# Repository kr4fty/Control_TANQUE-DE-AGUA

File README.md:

# Control de carga para TANQUE DE AGUA
 La función del circuito es la de encender/apagar un motor el cual llena un<br>
 tanque de agua. Sería reemplazo directo a los conocidos flotadores mecánicos.
<br>

<br>
## Objetivo
 El objetivo es la realización de un circuito que controle al motor, logrando<br>
 el llenado del tanque con la menor cantidad de encendidas. De esta forma se<br>
 intenta ahorrar energía, ya que al encender el motor este consume unas 6 veces<br>
 la corriente nominal de trabajo.<br>
 También se intentara diseñar el circuito con la menor cantidad de componentes y<br>
 de esta forma lograr que sea mas económico en comparación a los flotadores.<br>
 Y por ultimo, el objetivo final seria lograr ser el reemplazo directo, UNO a<br>
 UNO entre los dos dispositivos (electrónico - mecánico), no agregando mas<br>
 cables ni fuentes adicionales a los ya existentes.<br>

## Ventajas
 * Mas económico en comparación al flotador mecánico
 * Menor consumo de energía, ya que solo se activara cuando llegue al nivel<br>
   seteado
 * ...

## Desventajas
 * Fuente de continua, se debería agregar esta fuente para alimentar el control
 * Dependiendo los sensores utilizados, se debería hasta agujerear al taque

## Futuras Modificaciones por mi (Kr4fty)
 * ~~Utilizar una fuente capacitiva que me convierta los 220Vac a los 12Vdc~~
 * ~~Modificar/corregir el circuito, ya que por ejemplo si seteamos que el nivel<br>
   mínimo de agua a un 25% y este sensor falla, es decir queda ABIERTO, el<br>
   motor seguiría funcionando indefinidamente. Lo mismo sucede con el sensor de<br>
   75%~~
 * Optimizar el circuito para tratar de utilizar la menor cantidad de componen_<br>
   tes electrónicos

## Autor original
 [ELECTROALL](https://github.com/ELECTROALL)

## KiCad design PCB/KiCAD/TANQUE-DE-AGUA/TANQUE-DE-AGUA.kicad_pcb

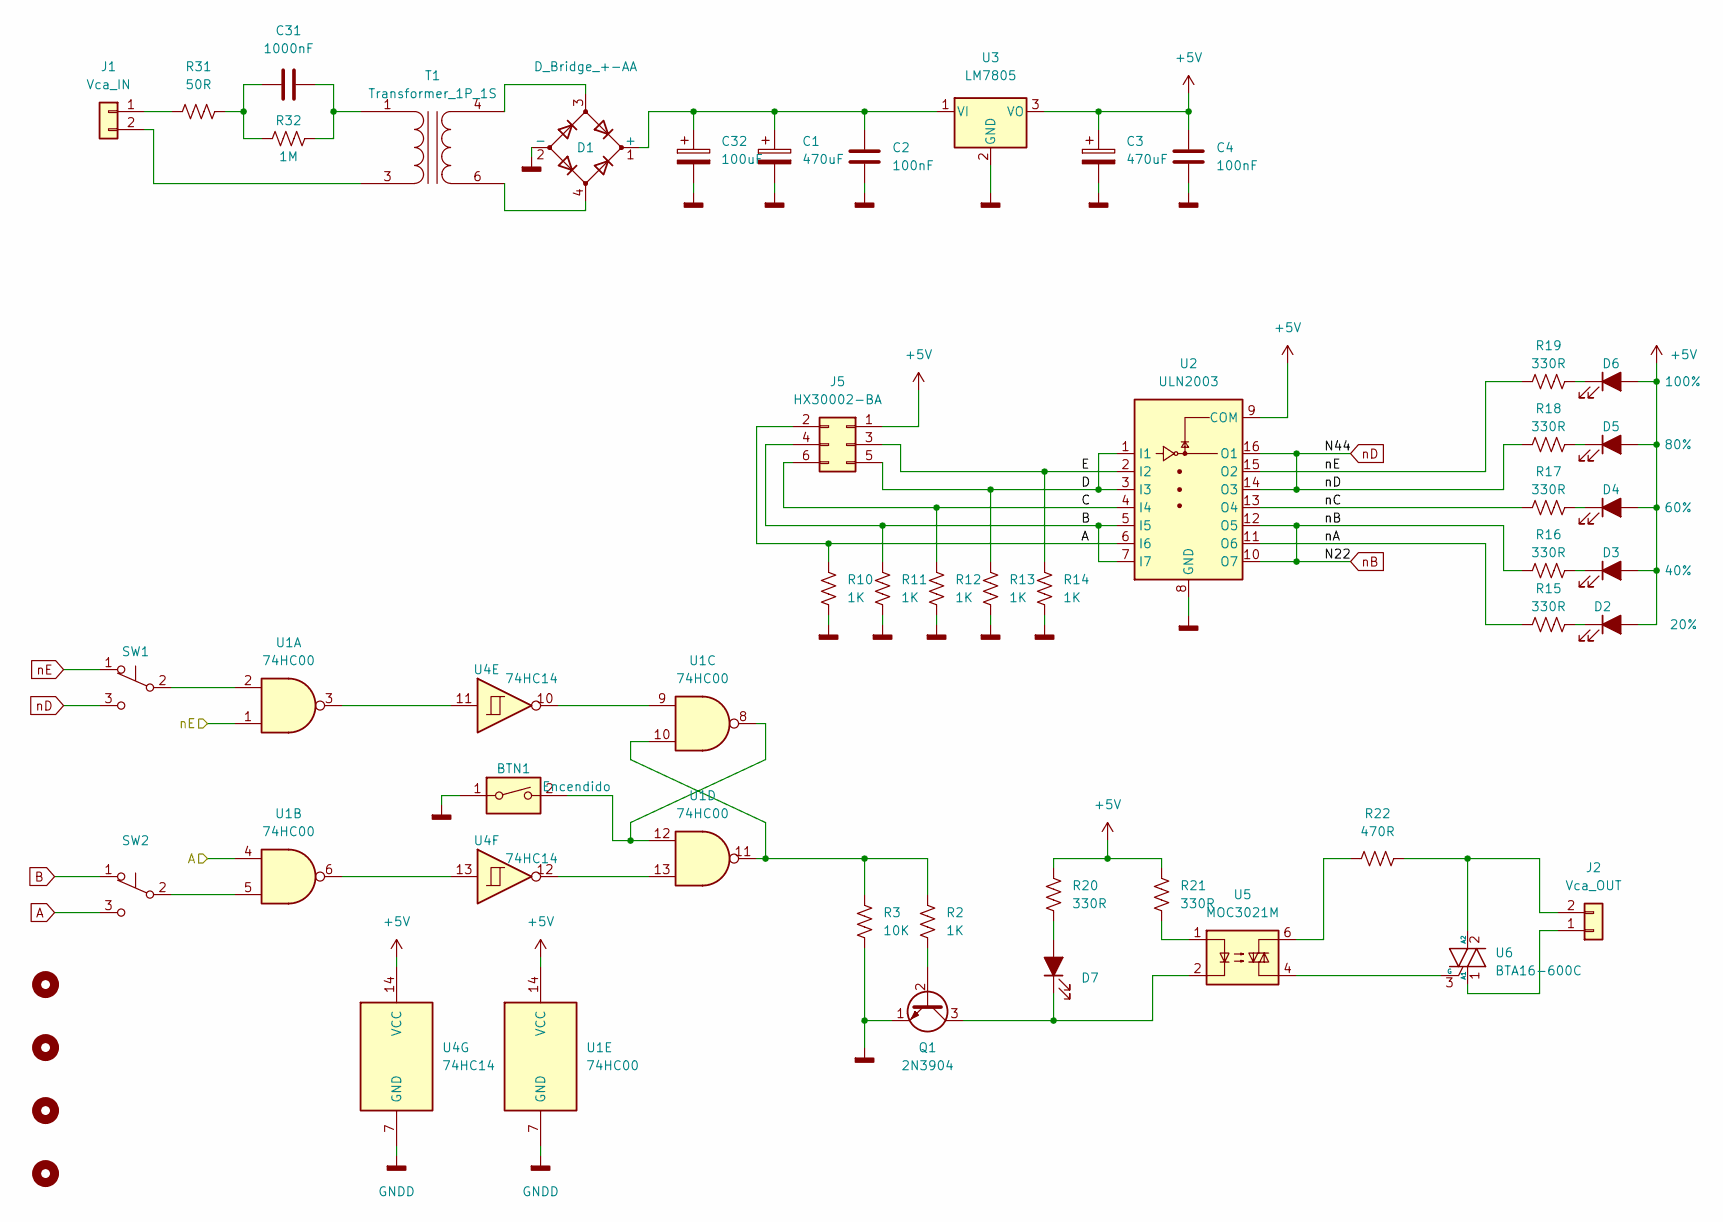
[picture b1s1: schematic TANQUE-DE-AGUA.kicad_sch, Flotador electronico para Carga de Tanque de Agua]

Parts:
BTN1: Encendido; SW_PUSH_6mm_H4.3mm
C1, C3: 470uF; CP_Radial_D8.0mm_P3.50mm
C2, C4: 100nF; C_Disc_D7.5mm_W2.5mm_P5.00mm
C31: 1000nF; C_Rect_L9.0mm_W4.0mm_P7.50mm_MKT
C32: 100uF; CP_Radial_D8.0mm_P3.50mm
D1: D_Bridge_+-AA; Diode_Bridge_19.0x3.5x10.0mm_P5.0mm
D2: 20%; LED_D3.0mm
D3: 40%; LED_D3.0mm
D4: 60%; LED_D3.0mm
D5: 80%; LED_D3.0mm
D6: 100%; LED_D3.0mm
D7: ENCENDIDO; LED_D3.0mm_IRGrey
H1, H2, H3, H4: MountingHole; MountingHole_4.3mm_M4
J1: Vca_IN; TerminalBlock_Phoenix_PT-1,5-2-5.0-H_1x02_P5.00mm_Horizontal
J2: Vca_OUT; TerminalBlock_Phoenix_PT-1,5-2-5.0-H_1x02_P5.00mm_Horizontal
J5: HX30002-BA; PinSocket_2x03_P2.54mm_Vertical
Q1: 2N3904; TO-92_Wide
R2, R10, R11, R12, R13, R14: 1K; R_Axial_DIN0207_L6.3mm_D2.5mm_P10.16mm_Horizontal
R3: 10K; R_Axial_DIN0207_L6.3mm_D2.5mm_P10.16mm_Horizontal
R15, R16, R17, R18, R19: 330R
R20, R21: 330R; R_Axial_DIN0207_L6.3mm_D2.5mm_P10.16mm_Horizontal
R22: 470R; R_Axial_DIN0207_L6.3mm_D2.5mm_P10.16mm_Horizontal
R31: 50R; R_Axial_DIN0207_L6.3mm_D2.5mm_P10.16mm_Horizontal
R32: 1M; R_Axial_DIN0207_L6.3mm_D2.5mm_P10.16mm_Horizontal
SW1: Nivel MAX; PinHeader_1x03_P2.54mm_Vertical
SW2: Nivel Min; PinHeader_1x03_P2.54mm_Vertical
T1: Transformer_1P_1S; Transformer_NF_ETAL_1-1_P1200
U1: 74HC00; DIP-14_W7.62mm_LongPads
U2: ULN2003; DIP-16_W7.62mm_LongPads
U3: LM7805; TO-220-3_Vertical
U4: 74HC14; DIP-14_W7.62mm_LongPads
U5: MOC3021M; DIP-6_W7.62mm_LongPads
U6: BTA16-600C; TO-220-3_Vertical

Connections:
+5V: C3.1, C4.1, D2.2 (A), D3.2 (A), D4.2 (A), D5.2 (A), D6.2 (A), J5.1, R20.1, R21.1, U1.14 (VCC), U2.9 (COM), U3.3 (VO), U4.14 (VCC)
/C: J5.6, R12.1, U2.4 (I4)
/D: J5.5, R13.1, U2.1 (I1), U2.3 (I3)
/E: J5.3, R14.1, U2.2 (I2)
/nA: R15.1, U2.11 (O6)
/nC: R17.1, U2.13 (O4)
A: J5.2, R10.1, SW2.3 (C), U1.4, U2.6 (I6)
B: J5.4, R11.1, SW2.1 (A), U2.5 (I5), U2.7 (I7)
GNDD: BTN1.1, C1.2, C2.2, C3.2, C4.2, C32.2, D1.2 (-), Q1.1 (E), R3.2, R10.2, R11.2, R12.2, R13.2, R14.2, U1.7 (GND), U2.8 (GND), U3.2 (GND), U4.7 (GND)
unnamed: BTN1.2, U1.8, U1.12
unnamed: C1.1, C2.1, C32.1, D1.1 (+), U3.1 (VI)
unnamed: C31.1, R31.2, R32.1
unnamed: C31.2, R32.2, T1.1 (AA)
unnamed: D1.3, T1.4 (SB)
unnamed: D1.4, T1.6 (SA)
unnamed: D2.1 (K), R15.2
unnamed: D3.1 (K), R16.2
unnamed: D4.1 (K), R17.2
unnamed: D5.1 (K), R18.2
unnamed: D6.1 (K), R19.2
unnamed: D7.1 (K), Q1.3 (C), U5.2
unnamed: D7.2 (A), R20.2
unnamed: J1.1, R31.1
unnamed: J1.2, T1.3 (AB)
unnamed: J2.1, U6.1 (A1)
unnamed: J2.2, R22.1, U6.2 (A2)
unnamed: Q1.2 (B), R2.2
unnamed: R2.1, R3.1, U1.10, U1.11
unnamed: R21.2, U5.1
unnamed: R22.2, U5.6
unnamed: SW1.2 (B), U1.2
unnamed: SW2.2 (B), U1.5
unnamed: U1.3, U4.11
unnamed: U1.6, U4.13
unnamed: U1.9, U4.10
unnamed: U1.13, U4.12
unnamed: U5.4, U6.3 (G)
nB: R16.1, U2.10 (O7), U2.12 (O5)
nD: R18.1, SW1.3 (C), U2.14 (O3), U2.16 (O1)
nE: R19.1, SW1.1 (A), U1.1, U2.15 (O2)

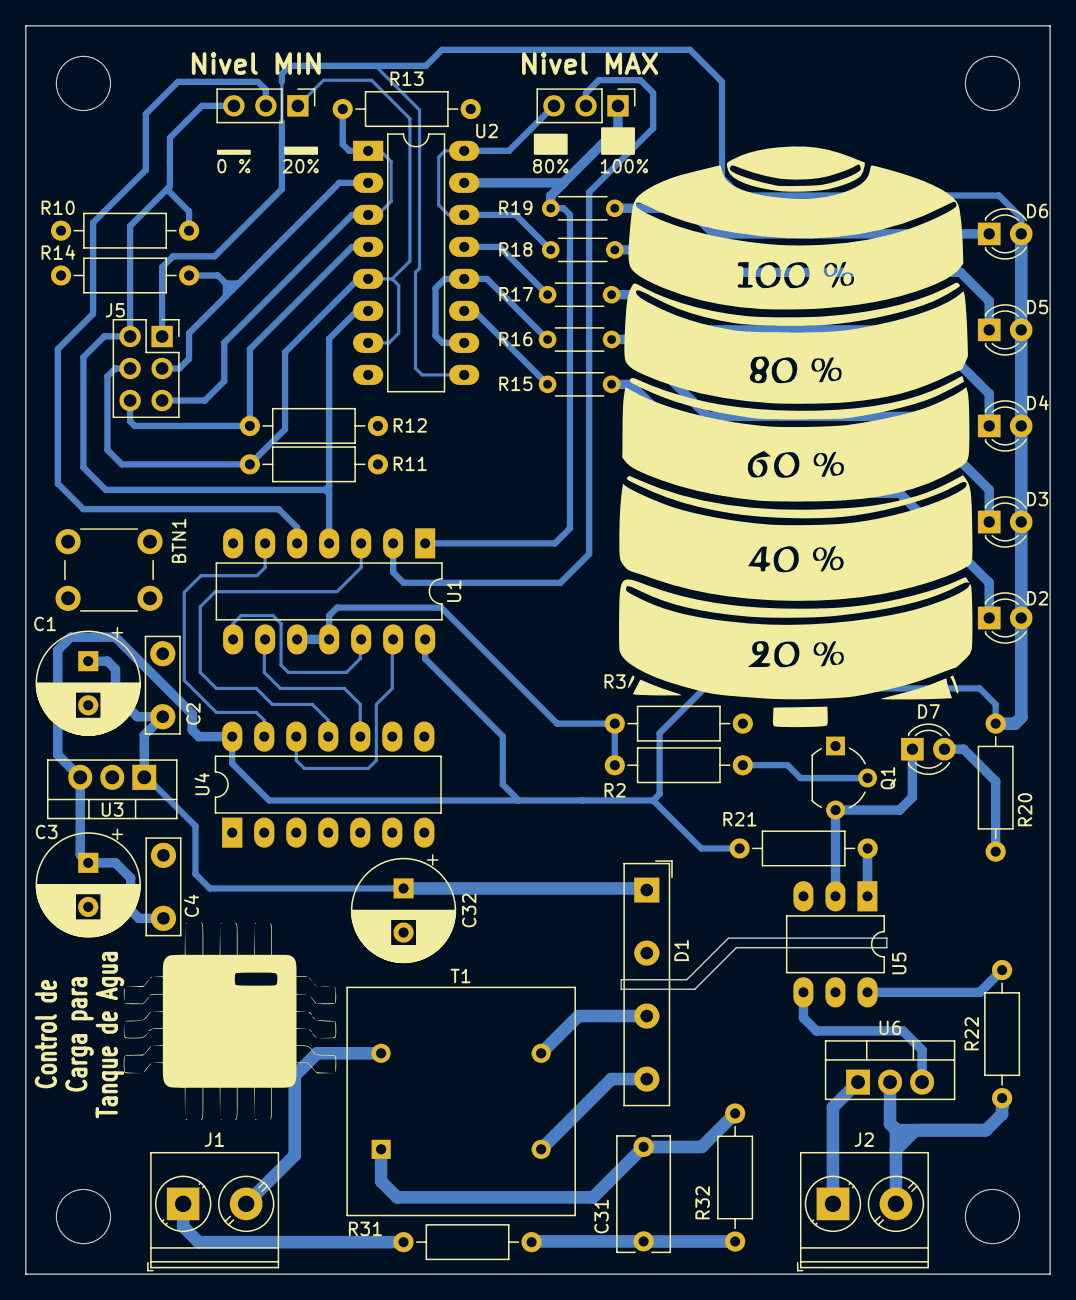
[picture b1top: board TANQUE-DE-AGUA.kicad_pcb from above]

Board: 2 copper layers, 81.3 x 99.1 mm, 49 parts (0 on the bottom side), 40 nets.

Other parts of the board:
G1: LOGO; Tanque

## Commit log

2022-05-03 comenzando con mi fork
2022-05-07 En caso de bloquedo de sensor, forzar apagado
2022-05-07 actualizacion del esquematico modificado
2022-05-09 Actualizacion del diagrama y primer bosquejo del PCB hecho en KiCAD
2022-05-09 actualizacion del esquematico en Proteus y en KiCAD
2022-05-09 actualizacion de la lista de materiales
2022-05-10 actualizacion del PCB
2022-05-10 add image
2022-05-10 update rendered image
2022-05-10 add board gif
2022-05-10 gif e imagen
2022-05-11 se agrega Fuente capacitiva
2022-05-12 update PCB
